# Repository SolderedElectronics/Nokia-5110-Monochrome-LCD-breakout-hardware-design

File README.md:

[SKU]: 333000

# --- Product name --- Hardware design

## About the product

|  |
| :----------------------------------------------------------: |
|      [Buy --- product name ----](https://www.solde.red/[SKU])      |

------ product description ------

## Repository contents

All Soldered Electronics hardware designed in KiCAD, and repositories are organized in the following way:

- CAD folder - contains KiCAD files (Schematics, Board, Panel Board), sorted by version. Change log lists all changes between versions.
- OUTPUTS - contains useful files, such as Bill of Materials (BOM), PDF of schematics, 3D .step file of the board and gerber files, sorted by version. 
- OUTPUTS -> Compliance - Certificates and useful legal stuff. 

## Want to contribute?

Please feel free to submit a pull request if you have any contributions. We encourage you to submit an issue or pull request if you find a bug. 

## About Soldered

At Soldered, we design and manufacture a wide selection of electronic products to help you turn your ideas into acts and bring you one step closer to your final project. Our products are intented for makers and crafted in-house by our experienced team in Osijek, Croatia. We believe that sharing is a crucial element for improvement and innovation, and we work hard to stay connected with all our makers regardless of their skill or experience level. Therefore, all our products are open-source. Finally, we always have your back. If you face any problem concerning either your shopping experience or your electronics project, our team will help you deal with it, offering efficient customer service and cost-free technical support anytime. Some of those might be useful for you:

- [Web Store](https://www.soldered.com/shop)
- [Tutorials & Projects](https://soldered.com/learn)
- [Community & Technical support](https://soldered.com/community)

## License info

All Soldered open-source hardware (OSH) is under The TAPR Open Hardware License. Read more in the LICENSE file. 

No warranty - all designs in this repository are distributed in the hope that they will be useful, but without any warranty. They are provided "AS IS", therefore without warranty of any kind, either expressed or implied. The entire quality and performance of what you do with the contents of this repository are your responsibility. In no event, Soldered Electronics will be liable for your damages, losses, including any general, special, incidental or consequential damage arising out of the use or inability to use the contents of this repository. 

## Have fun! 
And thank you from your fellow makers at Soldered Electronics.

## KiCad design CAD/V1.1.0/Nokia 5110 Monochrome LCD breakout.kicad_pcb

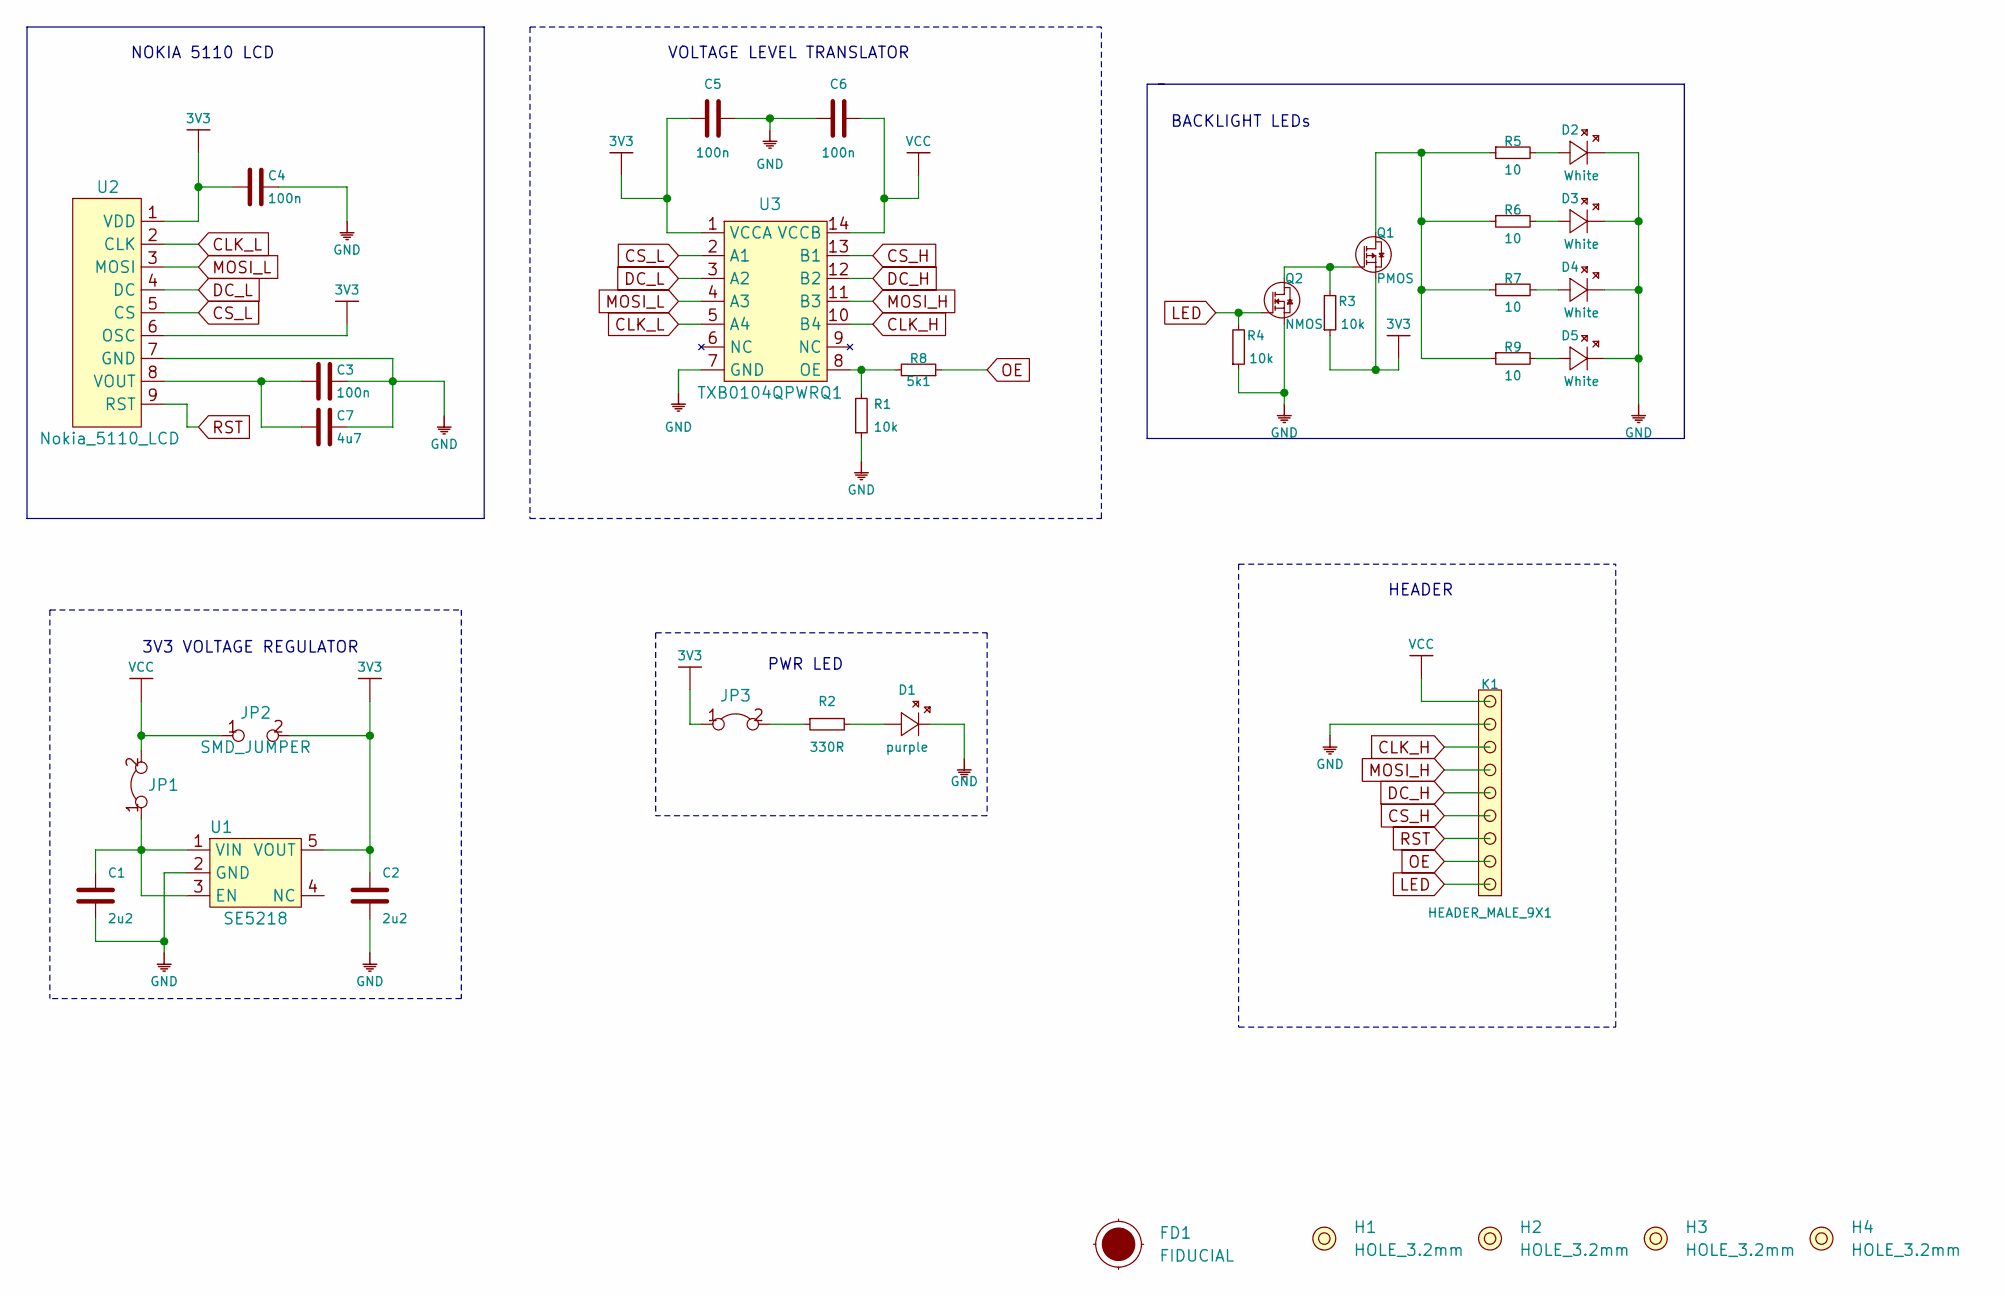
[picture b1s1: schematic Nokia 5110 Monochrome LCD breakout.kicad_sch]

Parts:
C1, C2: 2u2; 0603C
C3, C4, C5, C6: 100n; 0603C
C7: 4u7; 0603C
D1: purple; 0402LED
D2, D3, D4, D5: White; 0603LED
FD1: FIDUCIAL; FIDUCIAL_23
H1, H2, H3, H4: HOLE_3.2mm
JP1, JP3: SMD-JUMPER-CONNECTED_TRACE_SOLDERMASK
JP2: SMD_JUMPER
K1: HEADER_MALE_9X1
Q1: PMOS; SOT-23-3
Q2: NMOS; SOT-23-3
R1, R3, R4: 10k; 0603R
R2: 330R; 0402R
R5, R6, R7, R9: 10; 0603R
R8: 5k1; 0603R
U1: SE5218; SOT-23-5
U2: Nokia_5110_LCD
U3: TXB0104QPWRQ1

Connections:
3V3: C2.2, C4.2, C5.1, JP2.2, JP3.1, Q1.2 (S), R3.1, U1.5 (VOUT), U2.1 (VDD), U2.6 (OSC), U3.1 (VCCA)
CLK_H: K1.7, U3.10 (B4)
CLK_L: U2.2 (CLK), U3.5 (A4)
CS_H: K1.4, U3.13 (B1)
CS_L: U2.5 (CS), U3.2 (A1)
DC_H: K1.5, U3.12 (B2)
DC_L: U2.4 (DC), U3.3 (A2)
GND: C1.1, C2.1, C3.1, C4.1, C5.2, C6.1, C7.1, D1.2 (K), D2.2 (K), D3.2 (K), D4.2 (K), D5.2 (K), K1.8, Q2.2 (S), R1.1, R4.1, U1.2 (GND), U2.7 (GND), U3.7 (GND)
LED: K1.1, Q2.1 (G), R4.2
MOSI_H: K1.6, U3.11 (B3)
MOSI_L: U2.3 (MOSI), U3.4 (A3)
unnamed: C1.2, JP1.1, U1.1 (VIN), U1.3 (EN)
unnamed: C3.2, C7.2, U2.8 (VOUT)
unnamed: D1.1 (A), R2.2
unnamed: D2.1 (A), R5.2
unnamed: D3.1 (A), R6.2
unnamed: D4.1 (A), R7.2
unnamed: D5.1 (A), R9.2
unnamed: JP3.2, R2.1
unnamed: Q1.1 (G), Q2.3 (D), R3.2
unnamed: Q1.3 (D), R5.1, R6.1, R7.1, R9.1
unnamed: R1.2, R8.2, U3.8 (OE)
OE: K1.2, R8.1
RST: K1.3, U2.9 (RST)
VCC: C6.2, JP1.2, JP2.1, K1.9, U3.14 (VCCB)

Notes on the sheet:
HEADER
BACKLIGHT LEDs
3V3 VOLTAGE REGULATOR
VOLTAGE LEVEL TRANSLATOR
PWR LED
NOKIA 5110 LCD

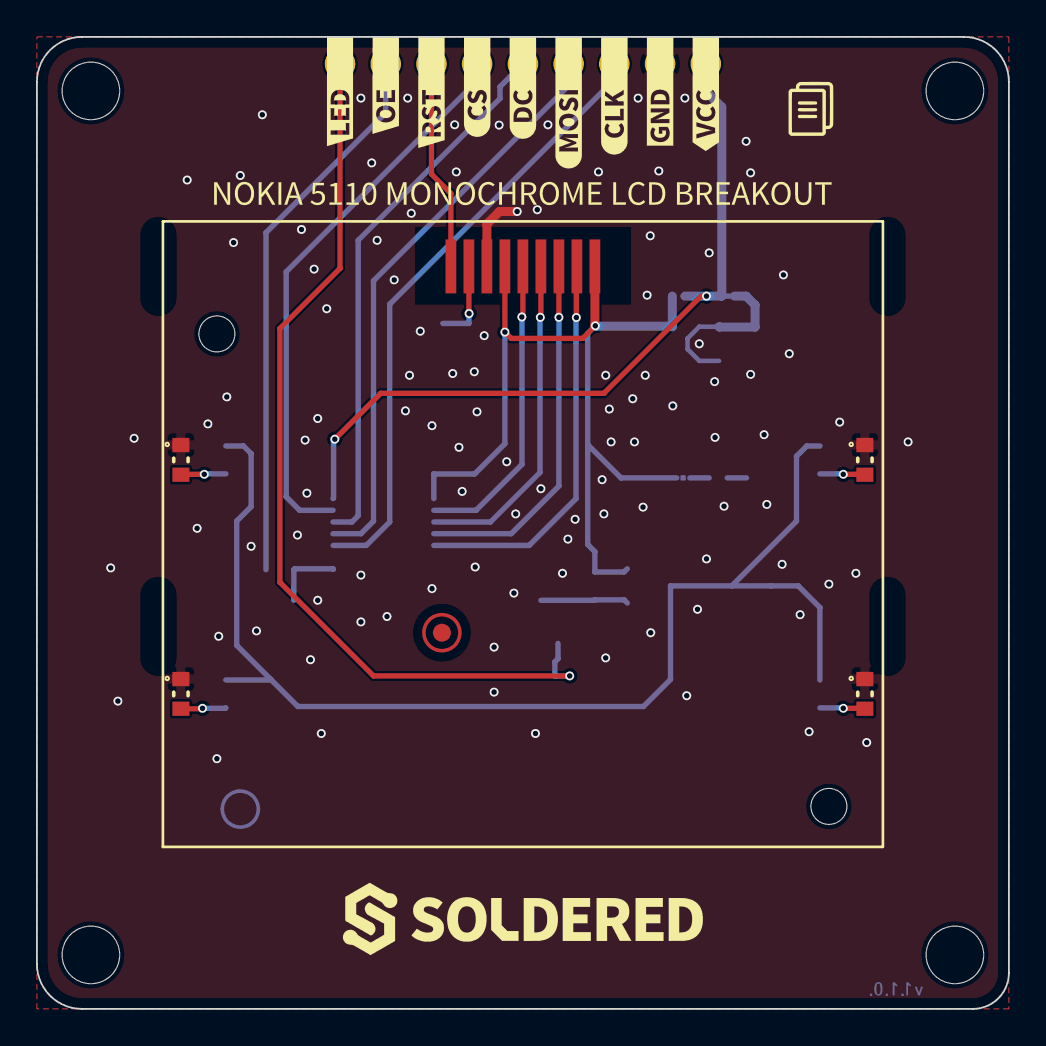
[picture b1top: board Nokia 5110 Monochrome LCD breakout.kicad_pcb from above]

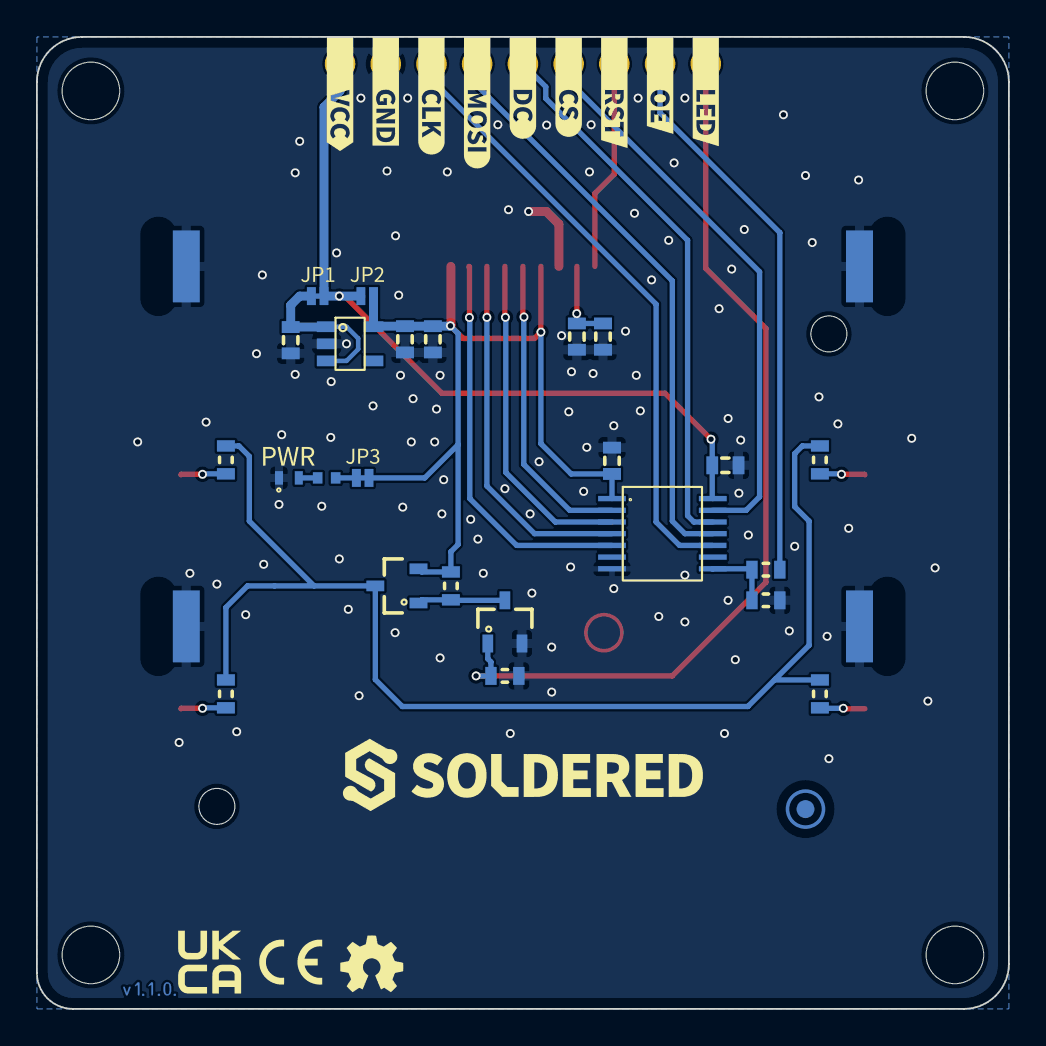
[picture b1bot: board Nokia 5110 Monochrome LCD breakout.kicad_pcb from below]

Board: 2 copper layers, 54.0 x 54.0 mm, 60 parts (40 on the bottom side), 25 nets.

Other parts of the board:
FD1#2: FIDUCIAL; FIDUCIAL_23
Ref**: Val**; Version1.1.0
kibuzzard-646B4D66: G***; kibuzzard-646B4D66
kibuzzard-640196A4: G***; kibuzzard-640196A4
kibuzzard-640198BB: G***; kibuzzard-640198BB
kibuzzard-640198C6: G***; kibuzzard-640198C6
kibuzzard-640198D2: G***; kibuzzard-640198D2
kibuzzard-640198DB: G***; kibuzzard-640198DB
kibuzzard-640198F2: G***; kibuzzard-640198F2
kibuzzard-6401968D: G***; kibuzzard-6401968D
kibuzzard-6401969B: G***; kibuzzard-6401969B
kibuzzard-6401969E: G***; kibuzzard-6401969E
kibuzzard-6401974E: G***; kibuzzard-6401974E
kibuzzard-6401977A: G***; kibuzzard-6401977A
kibuzzard-6401977E: G***; kibuzzard-6401977E
kibuzzard-6401983D: G***; kibuzzard-6401983D
kibuzzard-6401988B: G***; kibuzzard-6401988B
kibuzzard-6401989A: G***; kibuzzard-6401989A
kibuzzard-64019679: G***; kibuzzard-64019679
kibuzzard-64019690: G***; kibuzzard-64019690
kibuzzard-64019694: G***; kibuzzard-64019694
kibuzzard-64019697: G***; kibuzzard-64019697
kibuzzard-64019785: G***; kibuzzard-64019785
kibuzzard-64019789: G***; kibuzzard-64019789
kibuzzard-64019880: G***; kibuzzard-64019880

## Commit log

2024-10-20 Updating open source files.
